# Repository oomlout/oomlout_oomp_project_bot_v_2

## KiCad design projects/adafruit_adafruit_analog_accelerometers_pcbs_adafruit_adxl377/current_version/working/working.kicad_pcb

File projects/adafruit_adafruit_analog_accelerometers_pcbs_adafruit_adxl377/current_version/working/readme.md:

# adafruit_analog_accelerometers_pcbs
 
## summary 
* id: adafruit_adafruit_analog_accelerometers_pcbs_adafruit_adxl377
* user: adafruit
* name: adafruit_analog_accelerometers_pcbs
* board: adafruit_adxl377
* repo: https://github.com/adafruit/Adafruit-Analog-Accelerometers-PCBs

* src_file_repo_sch: 
* src_file_repo_sch_link: https://github.com/adafruit/Adafruit-Analog-Accelerometers-PCBs/tree/master/
* full details link: https://github.com/oomlout/oomlout_oomp_project_bot_v_2/tree/main/projects/adafruit_adafruit_analog_accelerometers_pcbs_adafruit_adxl377/current_version/working  

## schematic  
  
[schematic (pdf)](working_schematic.pdf) 

## pcb  

[board (pdf)](working.pdf)  

## working_bom
| Id | Designator | Footprint | Quantity | Designation | Supplier and ref |  | None | 
| --- | --- | --- | --- | --- | --- | --- | --- | 
| 1 | C2,C3,C4 | C0805K | 3 | 0.1uF |  |  | [''] | 
| 2 | C5,C1 | C0805K | 2 | 10uF |  |  | [''] | 
| 3 | JP2 | 1X07_ROUND_76 | 1 |  |  |  | [''] | 
| 4 | U$5,U$8 | MOUNTINGHOLE_2.0_PLATED | 2 | MOUNTINGHOLE2.0 |  |  | [''] | 
| 5 | IC1 | 16LCSP | 1 | ADXL33X |  |  | [''] | 
| 6 | U$1,U$2 | FIDUCIAL_1MM | 2 | FIDUCIAL |  |  | [''] | 
| 7 | IC2 | SOT23-5L | 1 | LP298XS |  |  | [''] | 
| 8 | U$4 | ADAFRUIT_2.5MM | 1 |  |  |  | [''] | 

## bom_schematic
| Ref | Qnty | Value | Cmp name | Footprint | Description | Vendor | DNP | 
| --- | --- | --- | --- | --- | --- | --- | --- | 
| C1, C5 | 2 | 10uF | C-USC0805K | working:C0805K |  |  |  | 
| C2, C3, C4 | 3 | 0.1uF | C-USC0805K | working:C0805K |  |  |  | 
| IC1 | 1 | ADXL33X | ADXL33X | working:16LCSP |  |  |  | 
| IC2 | 1 | LP298XS | LP298XS | working:SOT23-5L |  |  |  | 
| JP2 | 1 | HEADER-1X7THICKER | HEADER-1X7THICKER | working:1X07_ROUND_76 |  |  |  | 
| U$1, U$2 | 2 | FIDUCIAL | FIDUCIAL | working:FIDUCIAL_1MM |  |  |  | 
| U$5, U$8 | 2 | MOUNTINGHOLE2.0 | MOUNTINGHOLE2.0 | working:MOUNTINGHOLE_2.0_PLATED |  |  |  | 

## mounting_holes
| x | y | package | value | ref | size | 
| --- | --- | --- | --- | --- | --- | 
| 13.97 | 0.0 | MOUNTINGHOLE_2.0_PLATED | MOUNTINGHOLE2.0 | U$5 | m3 | 
| 0.0 | 0.0 | MOUNTINGHOLE_2.0_PLATED | MOUNTINGHOLE2.0 | U$8 | m3 |

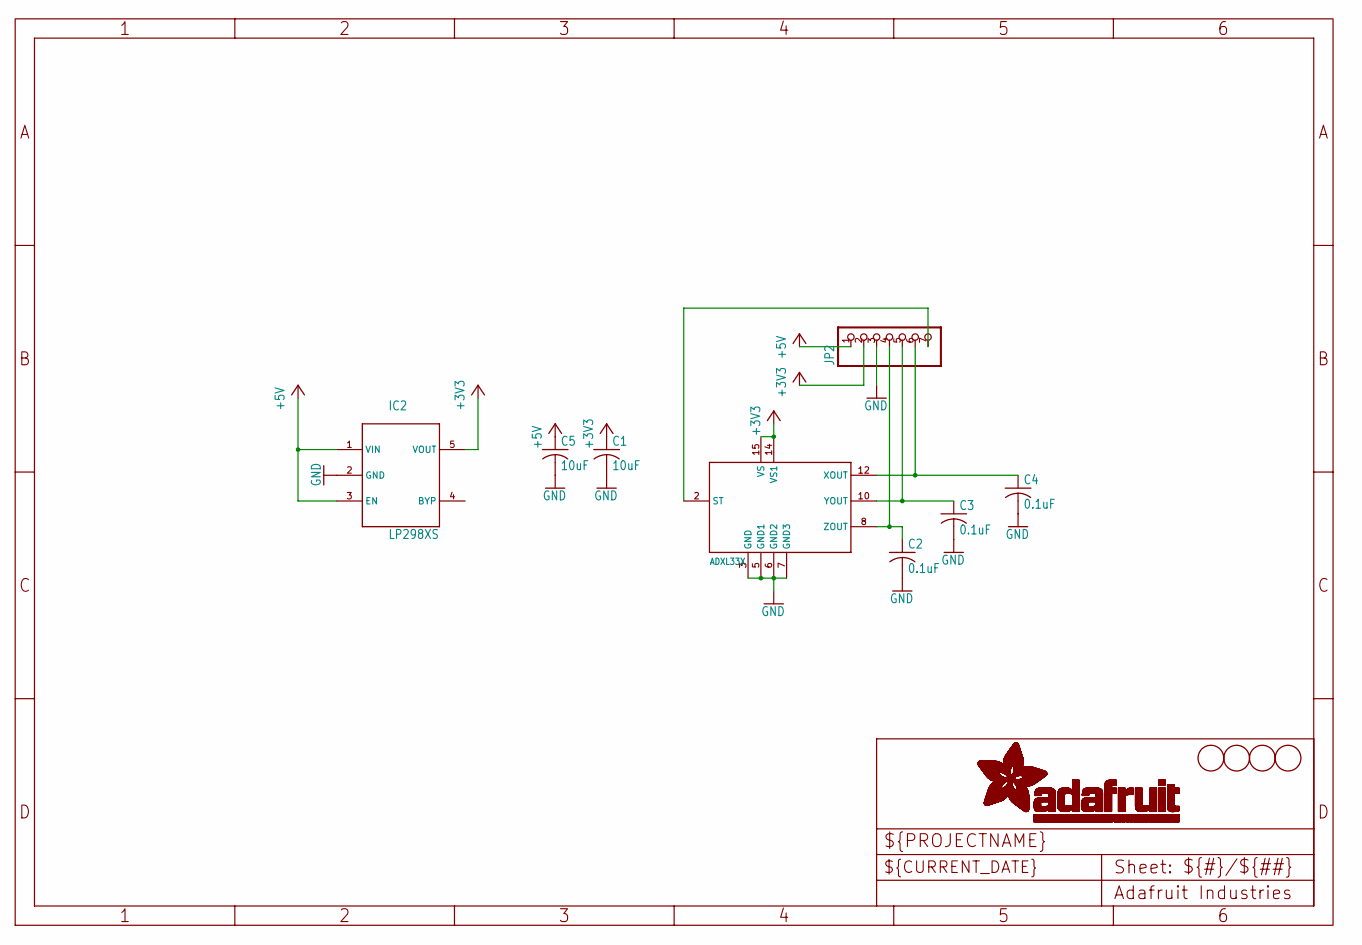
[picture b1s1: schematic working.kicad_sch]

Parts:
C1, C5: 10uF; C0805K
C2, C3, C4: 0.1uF; C0805K
IC1: ADXL33X; 16LCSP
IC2: LP298XS; SOT23-5L
JP2: HEADER-1X7THICKER; 1X07_ROUND_76
U$1, U$2: FIDUCIAL; FIDUCIAL_1MM
U$5, U$8: MOUNTINGHOLE2.0; MOUNTINGHOLE_2.0_PLATED

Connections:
+3V3: C1.1, IC1.14 (VS1), IC1.15 (VS), IC2.5 (VOUT), JP2.2
+5V: C5.1, IC2.1 (VIN), IC2.3 (EN), JP2.1
GND: C1.2, C2.2, C3.2, C4.2, C5.2, IC1.3 (GND), IC1.5 (GND1), IC1.6 (GND2), IC1.7 (GND3), IC2.2 (GND), JP2.3
ST: IC1.2 (ST), JP2.7
XOUT: C4.1, IC1.12 (XOUT), JP2.6
YOUT: C3.1, IC1.10 (YOUT), JP2.5
ZOUT: C2.1, IC1.8 (ZOUT), JP2.4

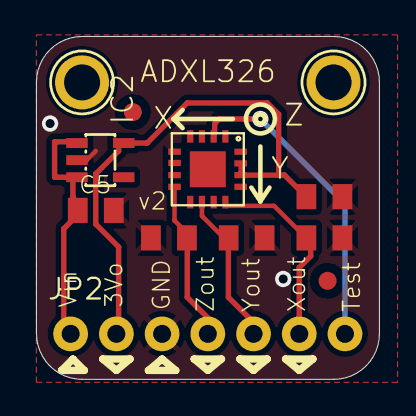
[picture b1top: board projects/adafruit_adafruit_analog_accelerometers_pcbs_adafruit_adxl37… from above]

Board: 16 copper layers, 19.1 x 19.1 mm, 13 parts (1 on the bottom side), 7 nets.

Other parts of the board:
U$4: ADAFRUIT_2.5MM

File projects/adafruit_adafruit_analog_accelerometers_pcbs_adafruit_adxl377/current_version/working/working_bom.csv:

"Id";"Designator";"Footprint";"Quantity";"Designation";"Supplier and ref";
1;"C2,C3,C4";"C0805K";3;"0.1uF";;;
2;"C5,C1";"C0805K";2;"10uF";;;
3;"JP2";"1X07_ROUND_76";1;"";;;
4;"U$5,U$8";"MOUNTINGHOLE_2.0_PLATED";2;"MOUNTINGHOLE2.0";;;
5;"IC1";"16LCSP";1;"ADXL33X";;;
6;"U$1,U$2";"FIDUCIAL_1MM";2;"FIDUCIAL";;;
7;"IC2";"SOT23-5L";1;"LP298XS";;;
8;"U$4";"ADAFRUIT_2.5MM";1;"";;;

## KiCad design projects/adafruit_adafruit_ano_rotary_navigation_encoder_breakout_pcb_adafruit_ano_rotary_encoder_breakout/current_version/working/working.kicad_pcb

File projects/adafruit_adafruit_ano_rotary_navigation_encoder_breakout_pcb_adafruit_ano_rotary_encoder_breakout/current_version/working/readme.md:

# adafruit_ano_rotary_navigation_encoder_breakout_pcb
 
## summary 
* id: adafruit_adafruit_ano_rotary_navigation_encoder_breakout_pcb_adafruit_ano_rotary_encoder_breakout
* user: adafruit
* name: adafruit_ano_rotary_navigation_encoder_breakout_pcb
* board: adafruit_ano_rotary_encoder_breakout
* repo: https://github.com/adafruit/Adafruit-ANO-Rotary-Navigation-Encoder-Breakout-PCB

* src_file_repo_sch: 
* src_file_repo_sch_link: https://github.com/adafruit/Adafruit-ANO-Rotary-Navigation-Encoder-Breakout-PCB/tree/main/
* full details link: https://github.com/oomlout/oomlout_oomp_project_bot_v_2/tree/main/projects/adafruit_adafruit_ano_rotary_navigation_encoder_breakout_pcb_adafruit_ano_rotary_encoder_breakout/current_version/working  

## schematic  
  
[schematic (pdf)](working_schematic.pdf) 

## pcb  

[board (pdf)](working.pdf)  

## working_bom
| Id | Designator | Footprint | Quantity | Designation | Supplier and ref |  | None | 
| --- | --- | --- | --- | --- | --- | --- | --- | 
| 1 | U$33 | PCBFEAT-REV-040 | 1 |  |  |  | [''] | 
| 2 | FID3,FID4 | FIDUCIAL_1MM | 2 | FIDUCIAL_1MM |  |  | [''] | 
| 3 | U$27,U$25,U$30,U$29 | MOUNTINGHOLE_2.5_PLATED | 4 | MOUNTINGHOLE2.5 |  |  | [''] | 
| 4 | JP3 | 1X09_ROUND_70 | 1 |  |  |  | [''] | 
| 5 | U$32 | ADAFRUIT_3.5MM | 1 |  |  |  | [''] | 
| 6 | X1 | ENCODER_ANO | 1 | ENCODER_ANO |  |  | [''] | 

## bom_schematic
| Ref | Qnty | Value | Cmp name | Footprint | Description | Vendor | DNP | 
| --- | --- | --- | --- | --- | --- | --- | --- | 
| FID3, FID4 | 2 | FIDUCIAL_1MM | FIDUCIAL_1MM | working:FIDUCIAL_1MM |  |  |  | 
| JP3 | 1 | HEADER-1X970MIL | HEADER-1X970MIL | working:1X09_ROUND_70 |  |  |  | 
| U$25, U$27, U$29, U$30 | 4 | MOUNTINGHOLE2.5 | MOUNTINGHOLE2.5 | working:MOUNTINGHOLE_2.5_PLATED |  |  |  | 
| X1 | 1 | ENCODER_ANO | ENCODER_ANO | working:ENCODER_ANO |  |  |  | 

## mounting_holes
| x | y | package | value | ref | size | 
| --- | --- | --- | --- | --- | --- | 
| 30.48 | 0.0 | MOUNTINGHOLE_2.5_PLATED | MOUNTINGHOLE2.5 | U$25 | m3 | 
| 0.0 | 0.0 | MOUNTINGHOLE_2.5_PLATED | MOUNTINGHOLE2.5 | U$27 | m3 | 
| 30.48 | 30.48 | MOUNTINGHOLE_2.5_PLATED | MOUNTINGHOLE2.5 | U$29 | m3 | 
| 0.0 | 30.48 | MOUNTINGHOLE_2.5_PLATED | MOUNTINGHOLE2.5 | U$30 | m3 |

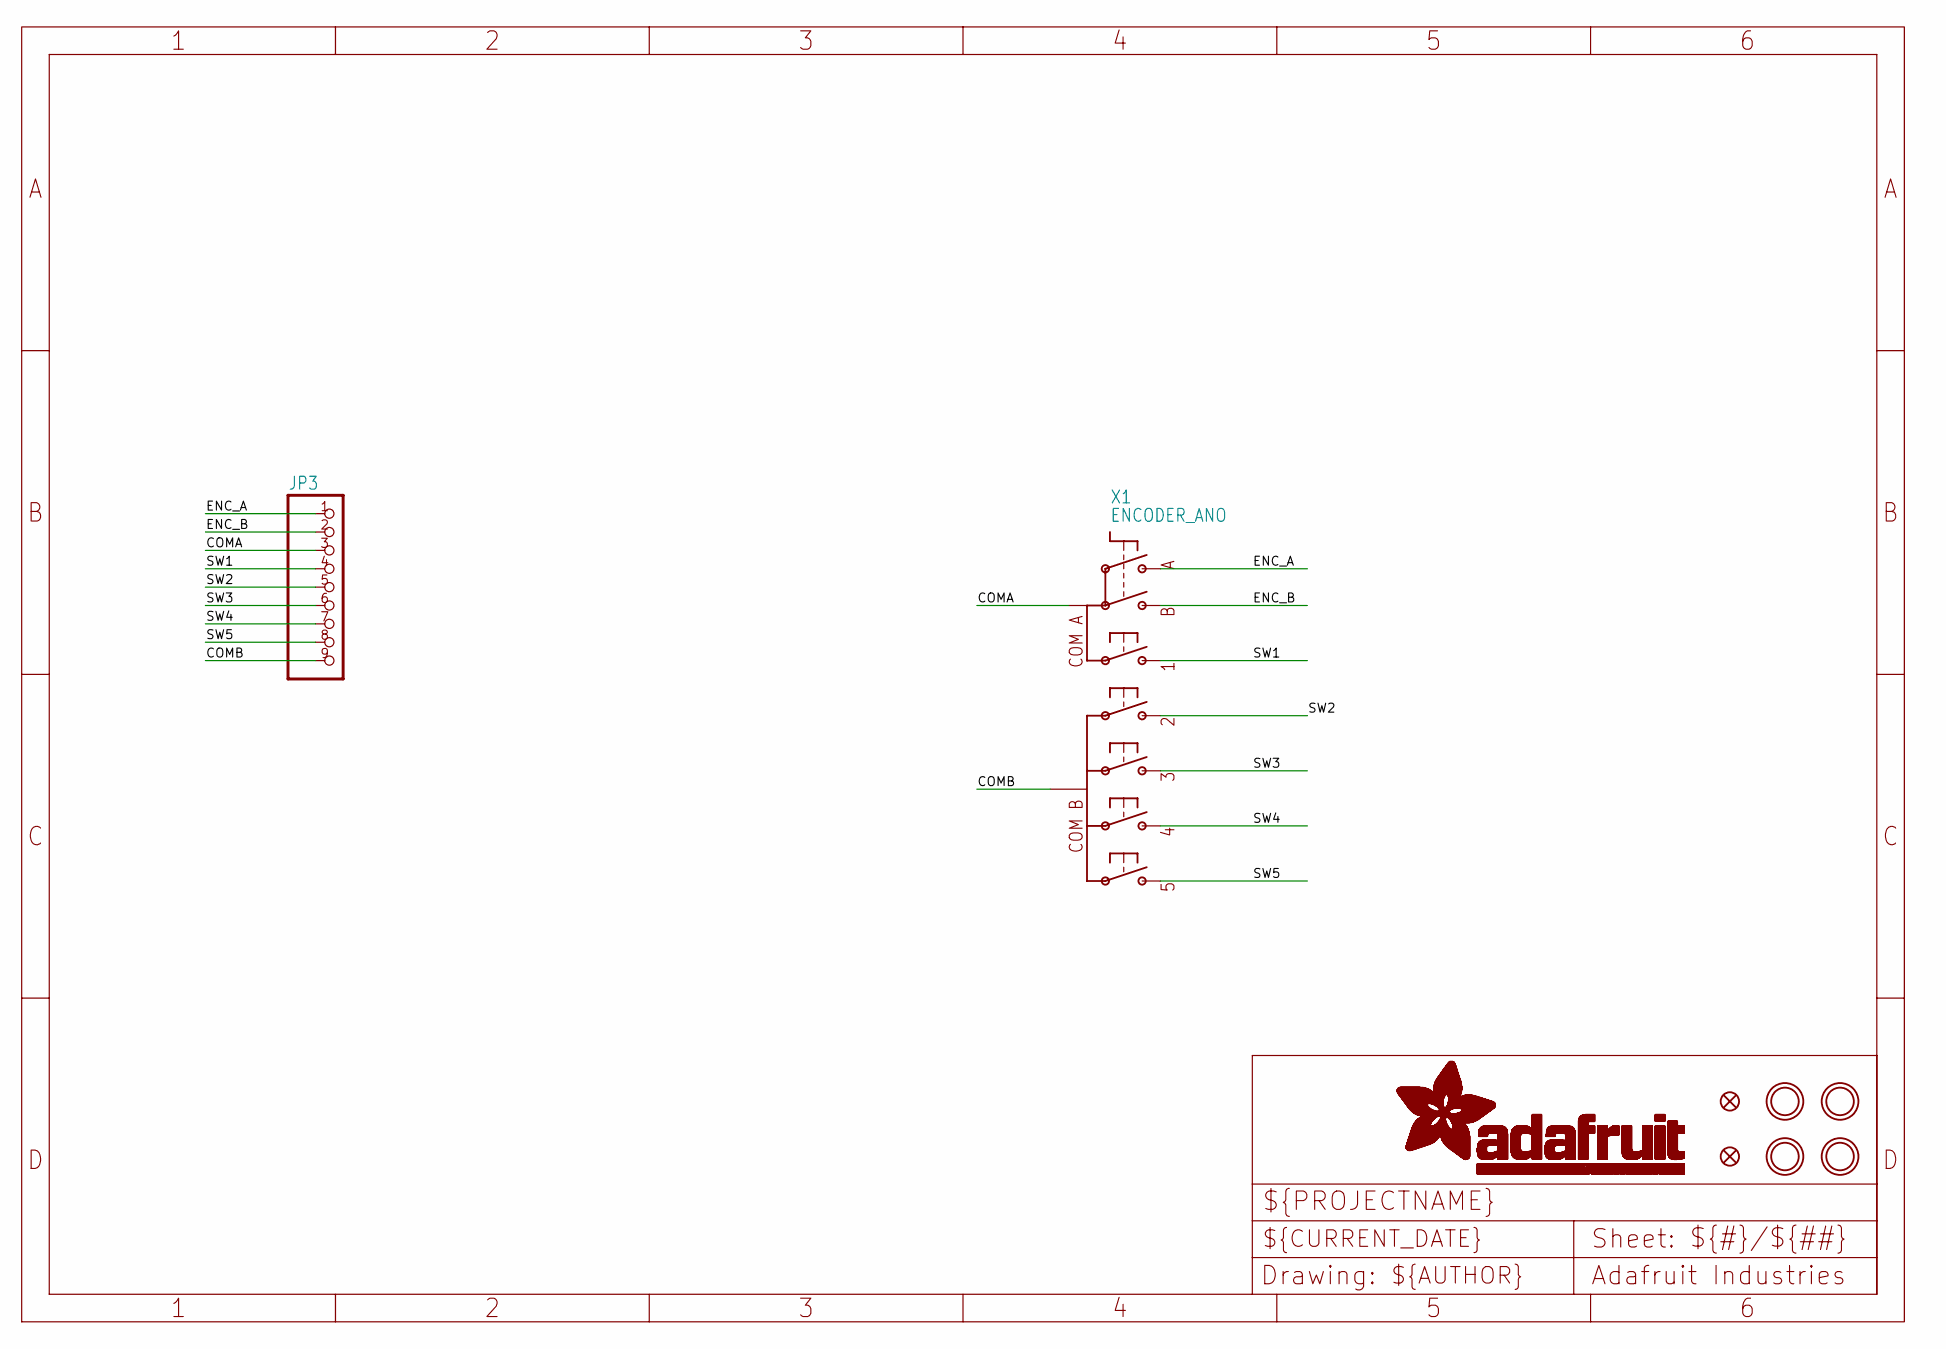
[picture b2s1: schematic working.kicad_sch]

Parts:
FID3, FID4: FIDUCIAL_1MM
JP3: HEADER-1X970MIL; 1X09_ROUND_70
U$25, U$27, U$29, U$30: MOUNTINGHOLE2.5; MOUNTINGHOLE_2.5_PLATED
X1: ENCODER_ANO

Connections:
COMA: JP3.3, X1.COM_A (COMA)
COMB: JP3.9, X1.COM_B
ENC_A: JP3.1, X1.A
ENC_B: JP3.2, X1.B
SW1: JP3.4, X1.S1 (1)
SW2: JP3.5, X1.S2
SW3: JP3.6, X1.S3
SW4: JP3.7, X1.S4
SW5: JP3.8, X1.S5

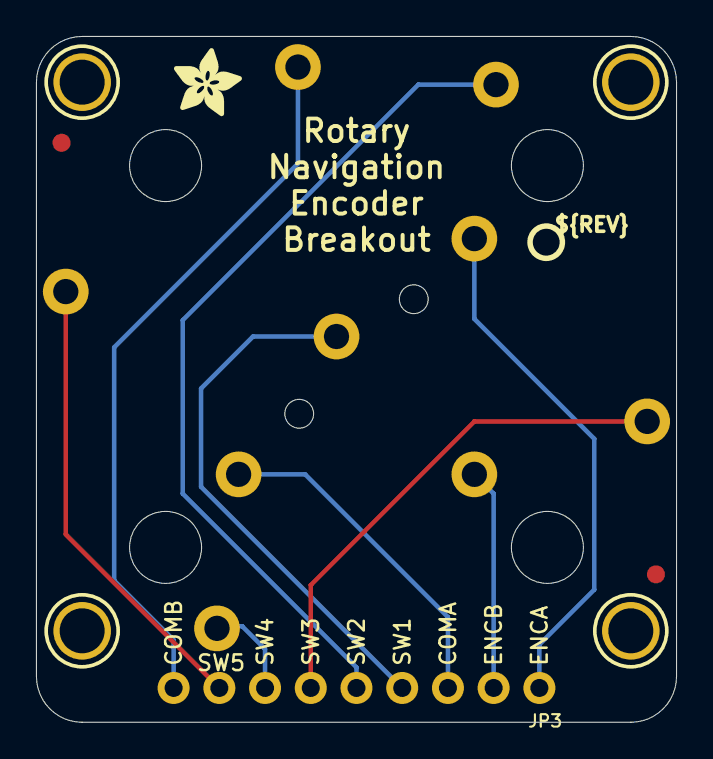
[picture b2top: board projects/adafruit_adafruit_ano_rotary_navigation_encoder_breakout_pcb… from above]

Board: 2 copper layers, 35.6 x 38.1 mm, 10 parts (1 on the bottom side), 9 nets.

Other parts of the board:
U$32: ADAFRUIT_3.5MM
U$33: PCBFEAT-REV-040

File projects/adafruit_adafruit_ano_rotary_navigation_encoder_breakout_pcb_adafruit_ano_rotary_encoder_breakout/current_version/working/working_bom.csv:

"Id";"Designator";"Footprint";"Quantity";"Designation";"Supplier and ref";
1;"U$33";"PCBFEAT-REV-040";1;"";;;
2;"FID3,FID4";"FIDUCIAL_1MM";2;"FIDUCIAL_1MM";;;
3;"U$27,U$25,U$30,U$29";"MOUNTINGHOLE_2.5_PLATED";4;"MOUNTINGHOLE2.5";;;
4;"JP3";"1X09_ROUND_70";1;"";;;
5;"U$32";"ADAFRUIT_3.5MM";1;"";;;
6;"X1";"ENCODER_ANO";1;"ENCODER_ANO";;;

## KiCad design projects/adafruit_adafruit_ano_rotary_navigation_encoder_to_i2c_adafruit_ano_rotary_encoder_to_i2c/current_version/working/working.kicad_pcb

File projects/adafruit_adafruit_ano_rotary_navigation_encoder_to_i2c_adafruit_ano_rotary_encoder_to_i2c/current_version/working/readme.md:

# adafruit_ano_rotary_navigation_encoder_to_i2c
 
## summary 
* id: adafruit_adafruit_ano_rotary_navigation_encoder_to_i2c_adafruit_ano_rotary_encoder_to_i2c
* user: adafruit
* name: adafruit_ano_rotary_navigation_encoder_to_i2c
* board: adafruit_ano_rotary_encoder_to_i2c
* repo: https://github.com/adafruit/Adafruit-ANO-Rotary-Navigation-Encoder-to-I2C

* src_file_repo_sch: 
* src_file_repo_sch_link: https://github.com/adafruit/Adafruit-ANO-Rotary-Navigation-Encoder-to-I2C/tree/main/
* full details link: https://github.com/oomlout/oomlout_oomp_project_bot_v_2/tree/main/projects/adafruit_adafruit_ano_rotary_navigation_encoder_to_i2c_adafruit_ano_rotary_encoder_to_i2c/current_version/working  

## schematic  
  
[schematic (pdf)](working_schematic.pdf) 

## pcb  

[board (pdf)](working.pdf)  

## working_bom
| Id | Designator | Footprint | Quantity | Designation | Supplier and ref |  | None | 
| --- | --- | --- | --- | --- | --- | --- | --- | 
| 1 | U$35,U$34 | STEMMAQT | 2 |  |  |  | [''] | 
| 2 | PLABEL10 | PLABEL10 | 1 |  |  |  | [''] | 
| 3 | FID3,FID4 | FIDUCIAL_1MM | 2 | FIDUCIAL_1MM |  |  | [''] | 
| 4 | U$30,U$29,U$25,U$27 | MOUNTINGHOLE_2.5_PLATED | 4 | MOUNTINGHOLE2.5 |  |  | [''] | 
| 5 | R4,R3,R1,R2,R7 | 0603-NO | 5 | 10K |  |  | [''] | 
| 6 | PLABEL4 | PLABEL4 | 1 |  |  |  | [''] | 
| 7 | PLABEL2 | PLABEL2 | 1 |  |  |  | [''] | 
| 8 | CONN4,CONN3 | JST_SH4 | 2 | STEMMA_I2C_QT |  |  | [''] | 
| 9 | U$2 | ADAFRUIT_5MM | 1 |  |  |  | [''] | 
| 10 | PLABEL9 | PLABEL9 | 1 |  |  |  | [''] | 
| 11 | X2 | QFN20_3MM | 1 | ATTINY8X6_QFN |  |  | [''] | 
| 12 | D1 | CHIPLED_0603_NOOUTLINE | 1 | GREEN |  |  | [''] | 
| 13 | SJ3,SJ2,SJ5,SJ4 | SOLDERJUMPER_CLOSEDWIRE | 4 |  |  |  | [''] | 
| 14 | C3,C2 | 0805-NO | 2 | 10uF |  |  | [''] | 
| 15 | D2 | CHIPLED_0603_NOOUTLINE | 1 | red |  |  | [''] | 
| 16 | PLABEL6 | PLABEL6 | 1 |  |  |  | [''] | 
| 17 | U$33 | PCBFEAT-REV-040 | 1 |  |  |  | [''] | 
| 18 | JP1 | 1X06_ROUND_70 | 1 |  |  |  | [''] | 
| 19 | PLABEL1 | PLABEL1 | 1 |  |  |  | [''] | 
| 20 | PLABEL0 | PLABEL0 | 1 |  |  |  | [''] | 
| 21 | R5 | RESPACK_4X0603 | 1 | 10K Pack |  |  | [''] | 
| 22 | PLABEL11 | PLABEL11 | 1 |  |  |  | [''] | 
| 23 | PLABEL3 | PLABEL3 | 1 |  |  |  | [''] | 
| 24 | PLABEL8 | PLABEL8 | 1 |  |  |  | [''] | 
| 25 | PLABEL5 | PLABEL5 | 1 |  |  |  | [''] | 
| 26 | PLABEL7 | PLABEL7 | 1 |  |  |  | [''] | 
| 27 | C4 | 0603-NO | 1 | 0.1uF |  |  | [''] | 
| 28 | E$2 | ADAFRUIT_2.5MM | 1 |  |  |  | [''] | 
| 29 | X1 | ENCODER_ANO | 1 | ENCODER_ANO |  |  | [''] | 

## bom_schematic
| Ref | Qnty | Value | Cmp name | Footprint | Description | Vendor | DNP | 
| --- | --- | --- | --- | --- | --- | --- | --- | 
| C2, C3 | 2 | 10uF | CAP_CERAMIC0805-NOOUTLINE | working:0805-NO |  |  |  | 
| C4 | 1 | 0.1uF | CAP_CERAMIC0603_NO | working:0603-NO |  |  |  | 
| CONN3, CONN4 | 2 | STEMMA_I2C_QT | STEMMA_I2C_QT | working:JST_SH4 |  |  |  | 
| D1 | 1 | GREEN | LED0603_NOOUTLINE | working:CHIPLED_0603_NOOUTLINE |  |  |  | 
| D2 | 1 | red | LED0603_NOOUTLINE | working:CHIPLED_0603_NOOUTLINE |  |  |  | 
| FID3, FID4 | 2 | FIDUCIAL_1MM | FIDUCIAL_1MM | working:FIDUCIAL_1MM |  |  |  | 
| JP1 | 1 | HEADER-1X670MIL | HEADER-1X670MIL | working:1X06_ROUND_70 |  |  |  | 
| R1, R2, R3, R4, R7 | 5 | 10K | RESISTOR_0603_NOOUT | working:0603-NO |  |  |  | 
| R5 | 1 | 10K Pack | RESISTOR_4PACK | working:RESPACK_4X0603 |  |  |  | 
| SJ2, SJ3, SJ4, SJ5 | 4 | SOLDERJUMPERCLOSED | SOLDERJUMPERCLOSED | working:SOLDERJUMPER_CLOSEDWIRE |  |  |  | 
| U$25, U$27, U$29, U$30 | 4 | MOUNTINGHOLE2.5 | MOUNTINGHOLE2.5 | working:MOUNTINGHOLE_2.5_PLATED |  |  |  | 
| X1 | 1 | ENCODER_ANO | ENCODER_ANO | working:ENCODER_ANO |  |  |  | 
| X2 | 1 | ATTINY8X6_QFN | ATTINY8X6_QFN | working:QFN20_3MM |  |  |  | 

## mounting_holes
| x | y | package | value | ref | size | 
| --- | --- | --- | --- | --- | --- | 
| 30.48 | 0.0 | MOUNTINGHOLE_2.5_PLATED | MOUNTINGHOLE2.5 | U$25 | m3 | 
| 0.0 | 0.0 | MOUNTINGHOLE_2.5_PLATED | MOUNTINGHOLE2.5 | U$27 | m3 | 
| 30.48 | 35.56 | MOUNTINGHOLE_2.5_PLATED | MOUNTINGHOLE2.5 | U$29 | m3 | 
| 0.0 | 35.56 | MOUNTINGHOLE_2.5_PLATED | MOUNTINGHOLE2.5 | U$30 | m3 |

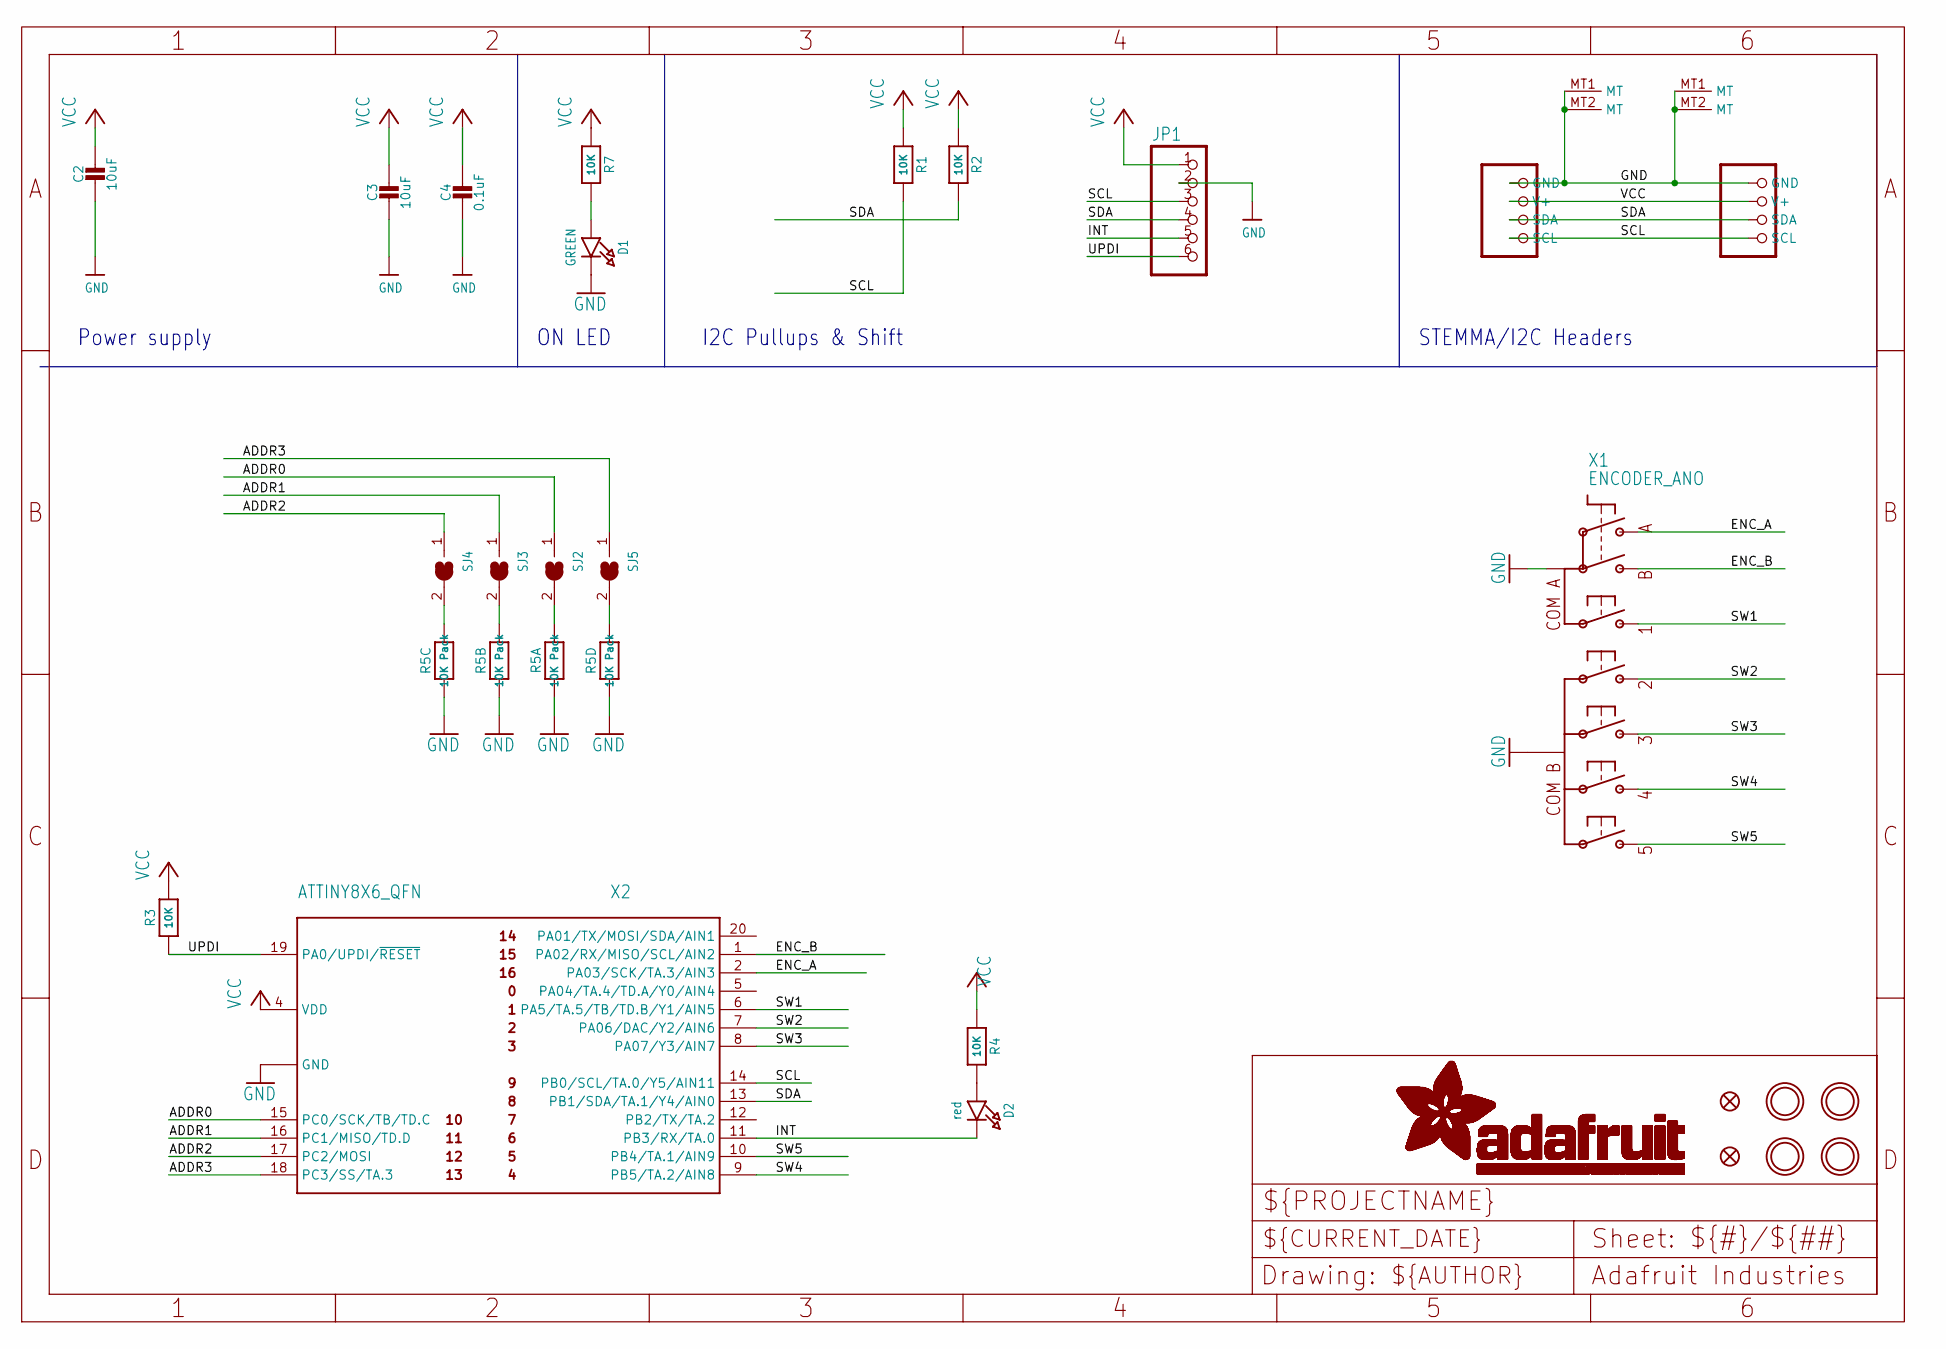
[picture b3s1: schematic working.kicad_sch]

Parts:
C2, C3: 10uF; 0805-NO
C4: 0.1uF; 0603-NO
CONN3, CONN4: STEMMA_I2C_QT; JST_SH4
D1: GREEN; CHIPLED_0603_NOOUTLINE
D2: red; CHIPLED_0603_NOOUTLINE
FID3, FID4: FIDUCIAL_1MM
JP1: HEADER-1X670MIL; 1X06_ROUND_70
R1, R2, R3, R4, R7: 10K; 0603-NO
R5: 10K Pack; RESPACK_4X0603
SJ2, SJ3, SJ4, SJ5: SOLDERJUMPERCLOSED; SOLDERJUMPER_CLOSEDWIRE
U$25, U$27, U$29, U$30: MOUNTINGHOLE2.5; MOUNTINGHOLE_2.5_PLATED
X1: ENCODER_ANO
X2: ATTINY8X6_QFN; QFN20_3MM

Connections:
ADDR0: SJ2.1, X2.15 (PC0/SCK/TB/TD.C)
ADDR1: SJ3.1, X2.16 (PC1/MISO/TD.D)
ADDR2: SJ4.1, X2.17 (PC2/MOSI)
ADDR3: SJ5.1, X2.18 (PC3/SS/TA.3)
ENC_A: X1.A, X2.2 (PA03/SCK/TA.3/AIN3)
ENC_B: X1.B, X2.1 (PA02/RX/MISO/SCL/AIN2)
GND: C2.2, C3.2, C4.2, CONN3.1 (GND), CONN3.MT1 (MT), CONN3.MT2 (MT), CONN4.1 (GND), CONN4.MT1 (MT), CONN4.MT2 (MT), D1.C, JP1.2, R5.1, R5.2 (1), R5.3 (1), R5.4 (1), X1.COM_A (COMA), X1.COM_B, X2.3 (GND), X2.PAD (GND)
INT: D2.C, JP1.5, X2.11 (PB3/RX/TA.0)
unnamed: D1.A, R7.2
unnamed: D2.A, R4.2
unnamed: R5.8 (2), SJ2.2
unnamed: R5.7 (2), SJ3.2
unnamed: R5.6 (2), SJ4.2
unnamed: R5.5 (2), SJ5.2
SCL: CONN3.4 (SCL), CONN4.4 (SCL), JP1.3, R1.2, X2.14 (PB0/SCL/TA.0/Y5/AIN11)
SDA: CONN3.3 (SDA), CONN4.3 (SDA), JP1.4, R2.2, X2.13 (PB1/SDA/TA.1/Y4/AIN0)
SW1: X1.S1 (1), X2.6 (PA5/TA.5/TB/TD.B/Y1/AIN5)
SW2: X1.S2, X2.7 (PA06/DAC/Y2/AIN6)
SW3: X1.S3, X2.8 (PA07/Y3/AIN7)
SW4: X1.S4, X2.9 (PB5/TA.2/AIN8)
SW5: X1.S5, X2.10 (PB4/TA.1/AIN9)
UPDI: JP1.6, R3.1, X2.19 (PA0/UPDI/~RESET)
VCC: C2.1, C3.1, C4.1, CONN3.2 (V+), CONN4.2 (V+), JP1.1, R1.1, R2.1, R3.2, R4.1, R7.1, X2.4 (VDD)

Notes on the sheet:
I2C Pullups & Shift
ON LED
STEMMA/I2C Headers
Power supply

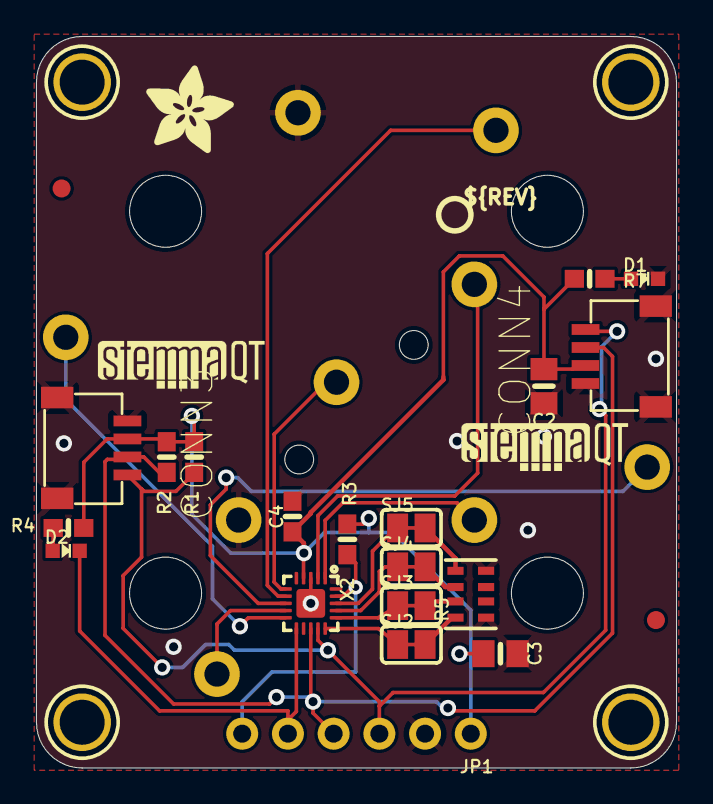
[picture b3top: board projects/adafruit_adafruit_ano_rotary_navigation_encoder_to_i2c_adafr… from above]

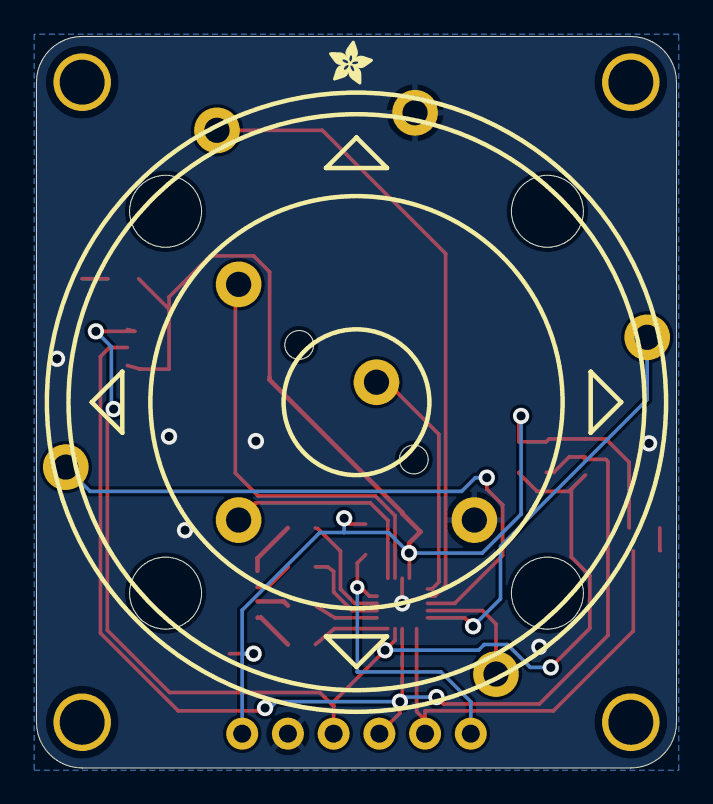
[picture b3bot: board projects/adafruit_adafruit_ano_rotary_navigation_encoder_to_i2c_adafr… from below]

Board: 2 copper layers, 35.6 x 40.6 mm, 43 parts (2 on the bottom side), 23 nets.

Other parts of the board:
E$2: ADAFRUIT_2.5MM
PLABEL0: PLABEL0
PLABEL1: PLABEL1
PLABEL2: PLABEL2
PLABEL3: PLABEL3
PLABEL4: PLABEL4
PLABEL5: PLABEL5
PLABEL6: PLABEL6
PLABEL7: PLABEL7
PLABEL8: PLABEL8
PLABEL9: PLABEL9
PLABEL10: PLABEL10
PLABEL11: PLABEL11
U$2: ADAFRUIT_5MM
U$33: PCBFEAT-REV-040
U$34, U$35: STEMMAQT

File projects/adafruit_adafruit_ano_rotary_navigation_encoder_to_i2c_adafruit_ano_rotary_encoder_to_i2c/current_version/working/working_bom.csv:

"Id";"Designator";"Footprint";"Quantity";"Designation";"Supplier and ref";
1;"U$35,U$34";"STEMMAQT";2;"";;;
2;"PLABEL10";"PLABEL10";1;"";;;
3;"FID3,FID4";"FIDUCIAL_1MM";2;"FIDUCIAL_1MM";;;
4;"U$30,U$29,U$25,U$27";"MOUNTINGHOLE_2.5_PLATED";4;"MOUNTINGHOLE2.5";;;
5;"R4,R3,R1,R2,R7";"0603-NO";5;"10K";;;
6;"PLABEL4";"PLABEL4";1;"";;;
7;"PLABEL2";"PLABEL2";1;"";;;
8;"CONN4,CONN3";"JST_SH4";2;"STEMMA_I2C_QT";;;
9;"U$2";"ADAFRUIT_5MM";1;"";;;
10;"PLABEL9";"PLABEL9";1;"";;;
11;"X2";"QFN20_3MM";1;"ATTINY8X6_QFN";;;
12;"D1";"CHIPLED_0603_NOOUTLINE";1;"GREEN";;;
13;"SJ3,SJ2,SJ5,SJ4";"SOLDERJUMPER_CLOSEDWIRE";4;"";;;
14;"C3,C2";"0805-NO";2;"10uF";;;
15;"D2";"CHIPLED_0603_NOOUTLINE";1;"red";;;
16;"PLABEL6";"PLABEL6";1;"";;;
17;"U$33";"PCBFEAT-REV-040";1;"";;;
18;"JP1";"1X06_ROUND_70";1;"";;;
19;"PLABEL1";"PLABEL1";1;"";;;
20;"PLABEL0";"PLABEL0";1;"";;;
21;"R5";"RESPACK_4X0603";1;"10K Pack";;;
22;"PLABEL11";"PLABEL11";1;"";;;
23;"PLABEL3";"PLABEL3";1;"";;;
24;"PLABEL8";"PLABEL8";1;"";;;
25;"PLABEL5";"PLABEL5";1;"";;;
26;"PLABEL7";"PLABEL7";1;"";;;
27;"C4";"0603-NO";1;"0.1uF";;;
28;"E$2";"ADAFRUIT_2.5MM";1;"";;;
29;"X1";"ENCODER_ANO";1;"ENCODER_ANO";;;

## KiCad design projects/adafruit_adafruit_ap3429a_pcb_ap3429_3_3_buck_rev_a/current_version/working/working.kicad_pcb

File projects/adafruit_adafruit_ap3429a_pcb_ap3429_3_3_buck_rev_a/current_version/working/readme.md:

# adafruit_ap3429a_pcb
 
## summary 
* id: adafruit_adafruit_ap3429a_pcb_ap3429_3_3_buck_rev_a
* user: adafruit
* name: adafruit_ap3429a_pcb
* board: ap3429_3_3_buck_rev_a
* repo: https://github.com/adafruit/Adafruit-AP3429A-PCB

* src_file_repo_sch: 
* src_file_repo_sch_link: https://github.com/adafruit/Adafruit-AP3429A-PCB/tree/main/
* full details link: https://github.com/oomlout/oomlout_oomp_project_bot_v_2/tree/main/projects/adafruit_adafruit_ap3429a_pcb_ap3429_3_3_buck_rev_a/current_version/working  

## schematic  
  
[schematic (pdf)](working_schematic.pdf) 

## pcb  

[board (pdf)](working.pdf)  

## bom_schematic
| Ref | Qnty | Value | Cmp name | Footprint | Description | Vendor | DNP | 
| --- | --- | --- | --- | --- | --- | --- | --- | 
| C1, C2, C3 | 3 | 22uF | CAP_CERAMIC0805-NOOUTLINE | working:0805-NO |  |  |  | 
| FID1 | 1 | FIDUCIAL_1MM | FIDUCIAL_1MM | working:FIDUCIAL_1MM |  |  |  | 
| IC1 | 1 | VREG_BUCK_5PIN_AP3429/A | VREG_BUCK_5PIN_AP3429/A | working:SOT23-5 |  |  |  | 
| JP1 | 1 | HEADER-1X4ROUND | HEADER-1X4ROUND | working:1X04_ROUND |  |  |  | 
| L1 | 1 | SDER041H-2R2MS | INDUCTORNRH2412T | working:INDUCTOR_TAIYOYUDEN_NRH2412T |  |  |  | 
| R1, R3 | 2 | 100K | RESISTOR_0603_NOOUT | working:0603-NO |  |  |  | 
| R2 | 1 | 450K | RESISTOR_0603_NOOUT | working:0603-NO |  |  |  | 
| U$9 | 1 | MOUNTINGHOLE2.5 | MOUNTINGHOLE2.5 | working:MOUNTINGHOLE_2.5_PLATED |  |  |  |

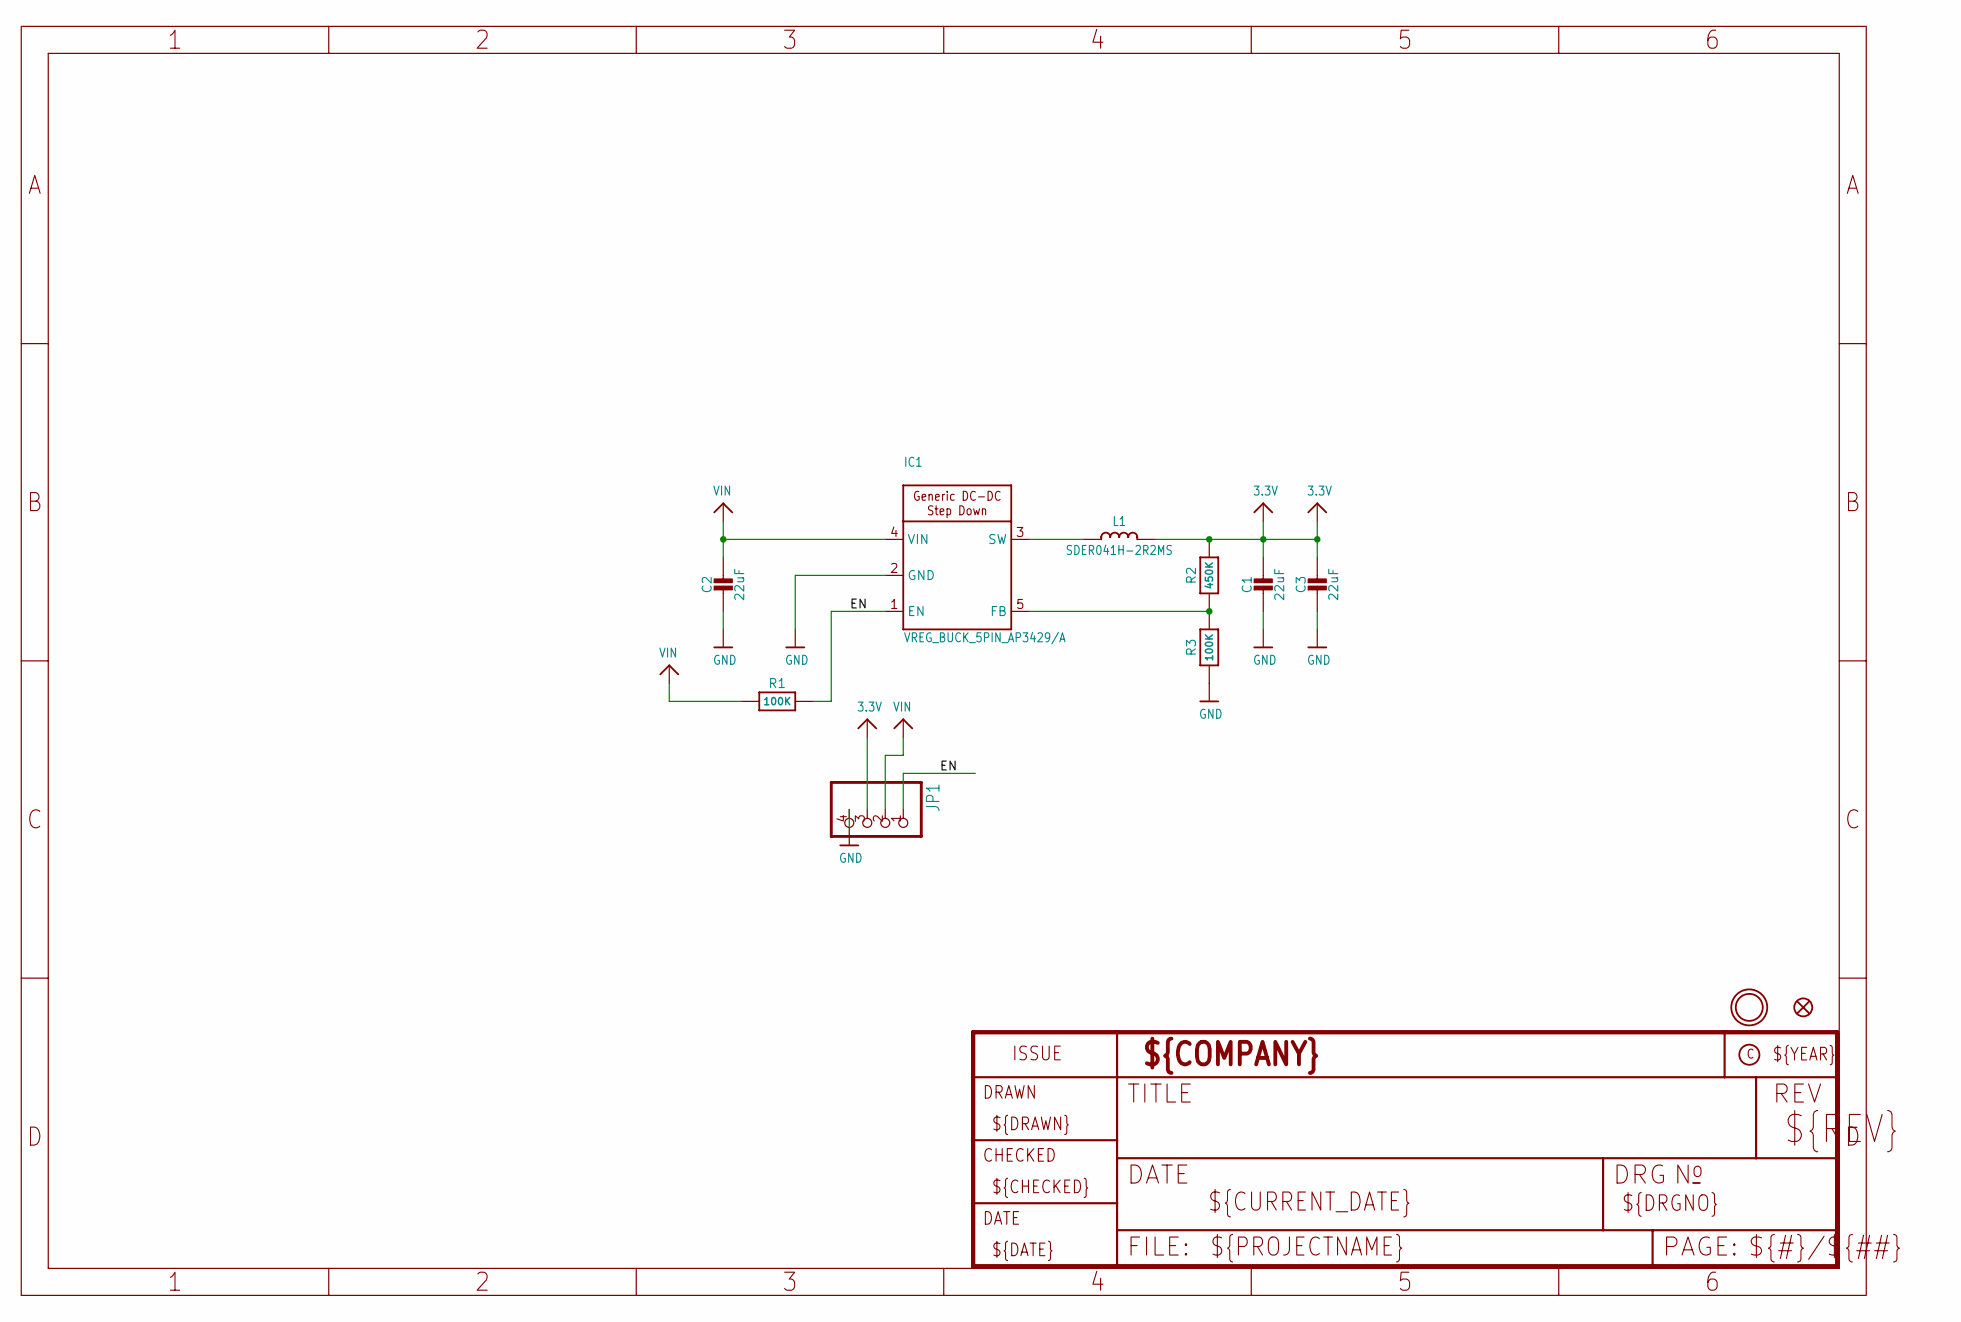
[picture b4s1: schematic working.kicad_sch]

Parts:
C1, C2, C3: 22uF; 0805-NO
FID1: FIDUCIAL_1MM
IC1: VREG_BUCK_5PIN_AP3429/A; SOT23-5
JP1: HEADER-1X4ROUND; 1X04_ROUND
L1: SDER041H-2R2MS; INDUCTOR_TAIYOYUDEN_NRH2412T
R1, R3: 100K; 0603-NO
R2: 450K; 0603-NO
U$9: MOUNTINGHOLE2.5; MOUNTINGHOLE_2.5_PLATED

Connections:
3.3V: C1.1, C3.1, JP1.3, L1.2, R2.2
EN: IC1.1 (EN), JP1.1, R1.2
FB: IC1.5 (FB), R2.1, R3.2
GND: C1.2, C2.2, C3.2, IC1.2 (GND), JP1.4, R3.1
unnamed: IC1.3 (SW), L1.1
VIN: C2.1, IC1.4 (VIN), JP1.2, R1.1

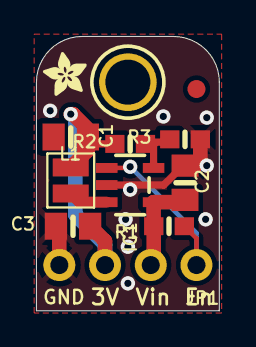
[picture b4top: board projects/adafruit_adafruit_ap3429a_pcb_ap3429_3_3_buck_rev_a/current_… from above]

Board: 2 copper layers, 10.2 x 15.2 mm, 13 parts (1 on the bottom side), 6 nets.

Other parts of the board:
U$10: PCBFEAT-REV-040
U$11: ADAFRUIT_2.5MM

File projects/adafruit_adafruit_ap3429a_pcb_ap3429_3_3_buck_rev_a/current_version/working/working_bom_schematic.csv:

"Source:","C:\gh\oomlout_oomp_project_bot_v_2\projects\adafruit_adafruit_ap3429a_pcb_ap3429_3_3_buck_rev_a\current_version\working\working.kicad_sch"
"Date:","09/09/2023 19:01:01"
"Tool:","Eeschema 7.0.6"
"Generator:","C:/Program Files/KiCad/7.0/bin/scripting/plugins/bom_csv_grouped_by_value_with_fp.py"
"Component Count:","11"
"Ref","Qnty","Value","Cmp name","Footprint","Description","Vendor","DNP"
"C1, C2, C3","3","22uF","CAP_CERAMIC0805-NOOUTLINE","working:0805-NO","","",""
"FID1","1","FIDUCIAL_1MM","FIDUCIAL_1MM","working:FIDUCIAL_1MM","","",""
"IC1","1","VREG_BUCK_5PIN_AP3429/A","VREG_BUCK_5PIN_AP3429/A","working:SOT23-5","","",""
"JP1","1","HEADER-1X4ROUND","HEADER-1X4ROUND","working:1X04_ROUND","","",""
"L1","1","SDER041H-2R2MS","INDUCTORNRH2412T","working:INDUCTOR_TAIYOYUDEN_NRH2412T","","",""
"R1, R3","2","100K","RESISTOR_0603_NOOUT","working:0603-NO","","",""
"R2","1","450K","RESISTOR_0603_NOOUT","working:0603-NO","","",""
"U$9","1","MOUNTINGHOLE2.5","MOUNTINGHOLE2.5","working:MOUNTINGHOLE_2.5_PLATED","","",""

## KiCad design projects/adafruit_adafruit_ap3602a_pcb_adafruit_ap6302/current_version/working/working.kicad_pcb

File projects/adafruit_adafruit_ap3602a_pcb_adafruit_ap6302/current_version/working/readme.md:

# adafruit_ap3602a_pcb
 
## summary 
* id: adafruit_adafruit_ap3602a_pcb_adafruit_ap6302
* user: adafruit
* name: adafruit_ap3602a_pcb
* board: adafruit_ap6302
* repo: https://github.com/adafruit/Adafruit-AP3602A-PCB

* src_file_repo_sch: 
* src_file_repo_sch_link: https://github.com/adafruit/Adafruit-AP3602A-PCB/tree/master/
* full details link: https://github.com/oomlout/oomlout_oomp_project_bot_v_2/tree/main/projects/adafruit_adafruit_ap3602a_pcb_adafruit_ap6302/current_version/working  

## schematic  
  
[schematic (pdf)](working_schematic.pdf) 

## pcb  

[board (pdf)](working.pdf)  

## working_bom
| Id | Designator | Footprint | Quantity | Designation | Supplier and ref |  | None | 
| --- | --- | --- | --- | --- | --- | --- | --- | 
| 1 | C3 | 0805-NO | 1 | 1uF |  |  | [''] | 
| 2 | C2,C1 | 0805-NO | 2 | 10uF |  |  | [''] | 
| 3 | JP1 | 1X04_ROUND | 1 |  |  |  | [''] | 
| 4 | U$9 | MOUNTINGHOLE_2.5_PLATED | 1 | MOUNTINGHOLE2.5 |  |  | [''] | 
| 5 | FID1 | FIDUCIAL_1MM | 1 | FIDUCIAL" |  |  | [''] | 
| 6 | U$11 | ADAFRUIT_2.5MM | 1 |  |  |  | [''] | 
| 7 | IC1 | SOT23-6 | 1 | AP3602 |  |  | [''] | 
| 8 | R1 | 0805-NO | 1 | 100K |  |  | [''] | 
| 9 | U$10 | PCBFEAT-REV-040 | 1 |  |  |  | [''] | 

## bom_schematic
| Ref | Qnty | Value | Cmp name | Footprint | Description | Vendor | DNP | 
| --- | --- | --- | --- | --- | --- | --- | --- | 
| C1, C2 | 2 | 10uF | CAP_CERAMIC0805-NOOUTLINE | working:0805-NO |  |  |  | 
| C3 | 1 | 1uF | CAP_CERAMIC0805-NOOUTLINE | working:0805-NO |  |  |  | 
| FID1 | 1 | FIDUCIAL"" | FIDUCIAL{dblquote}{dblquote} | working:FIDUCIAL_1MM |  |  |  | 
| IC1 | 1 | AP3602 | AP3602 | working:SOT23-6 |  |  |  | 
| JP1 | 1 | HEADER-1X4ROUND | HEADER-1X4ROUND | working:1X04_ROUND |  |  |  | 
| R1 | 1 | 100K | RESISTOR0805_NOOUTLINE | working:0805-NO |  |  |  | 
| U$9 | 1 | MOUNTINGHOLE2.5 | MOUNTINGHOLE2.5 | working:MOUNTINGHOLE_2.5_PLATED |  |  |  | 

## mounting_holes
| x | y | package | value | ref | size | 
| --- | --- | --- | --- | --- | --- | 
| 0.0 | 0.0 | MOUNTINGHOLE_2.5_PLATED | MOUNTINGHOLE2.5 | U$9 | m3 |

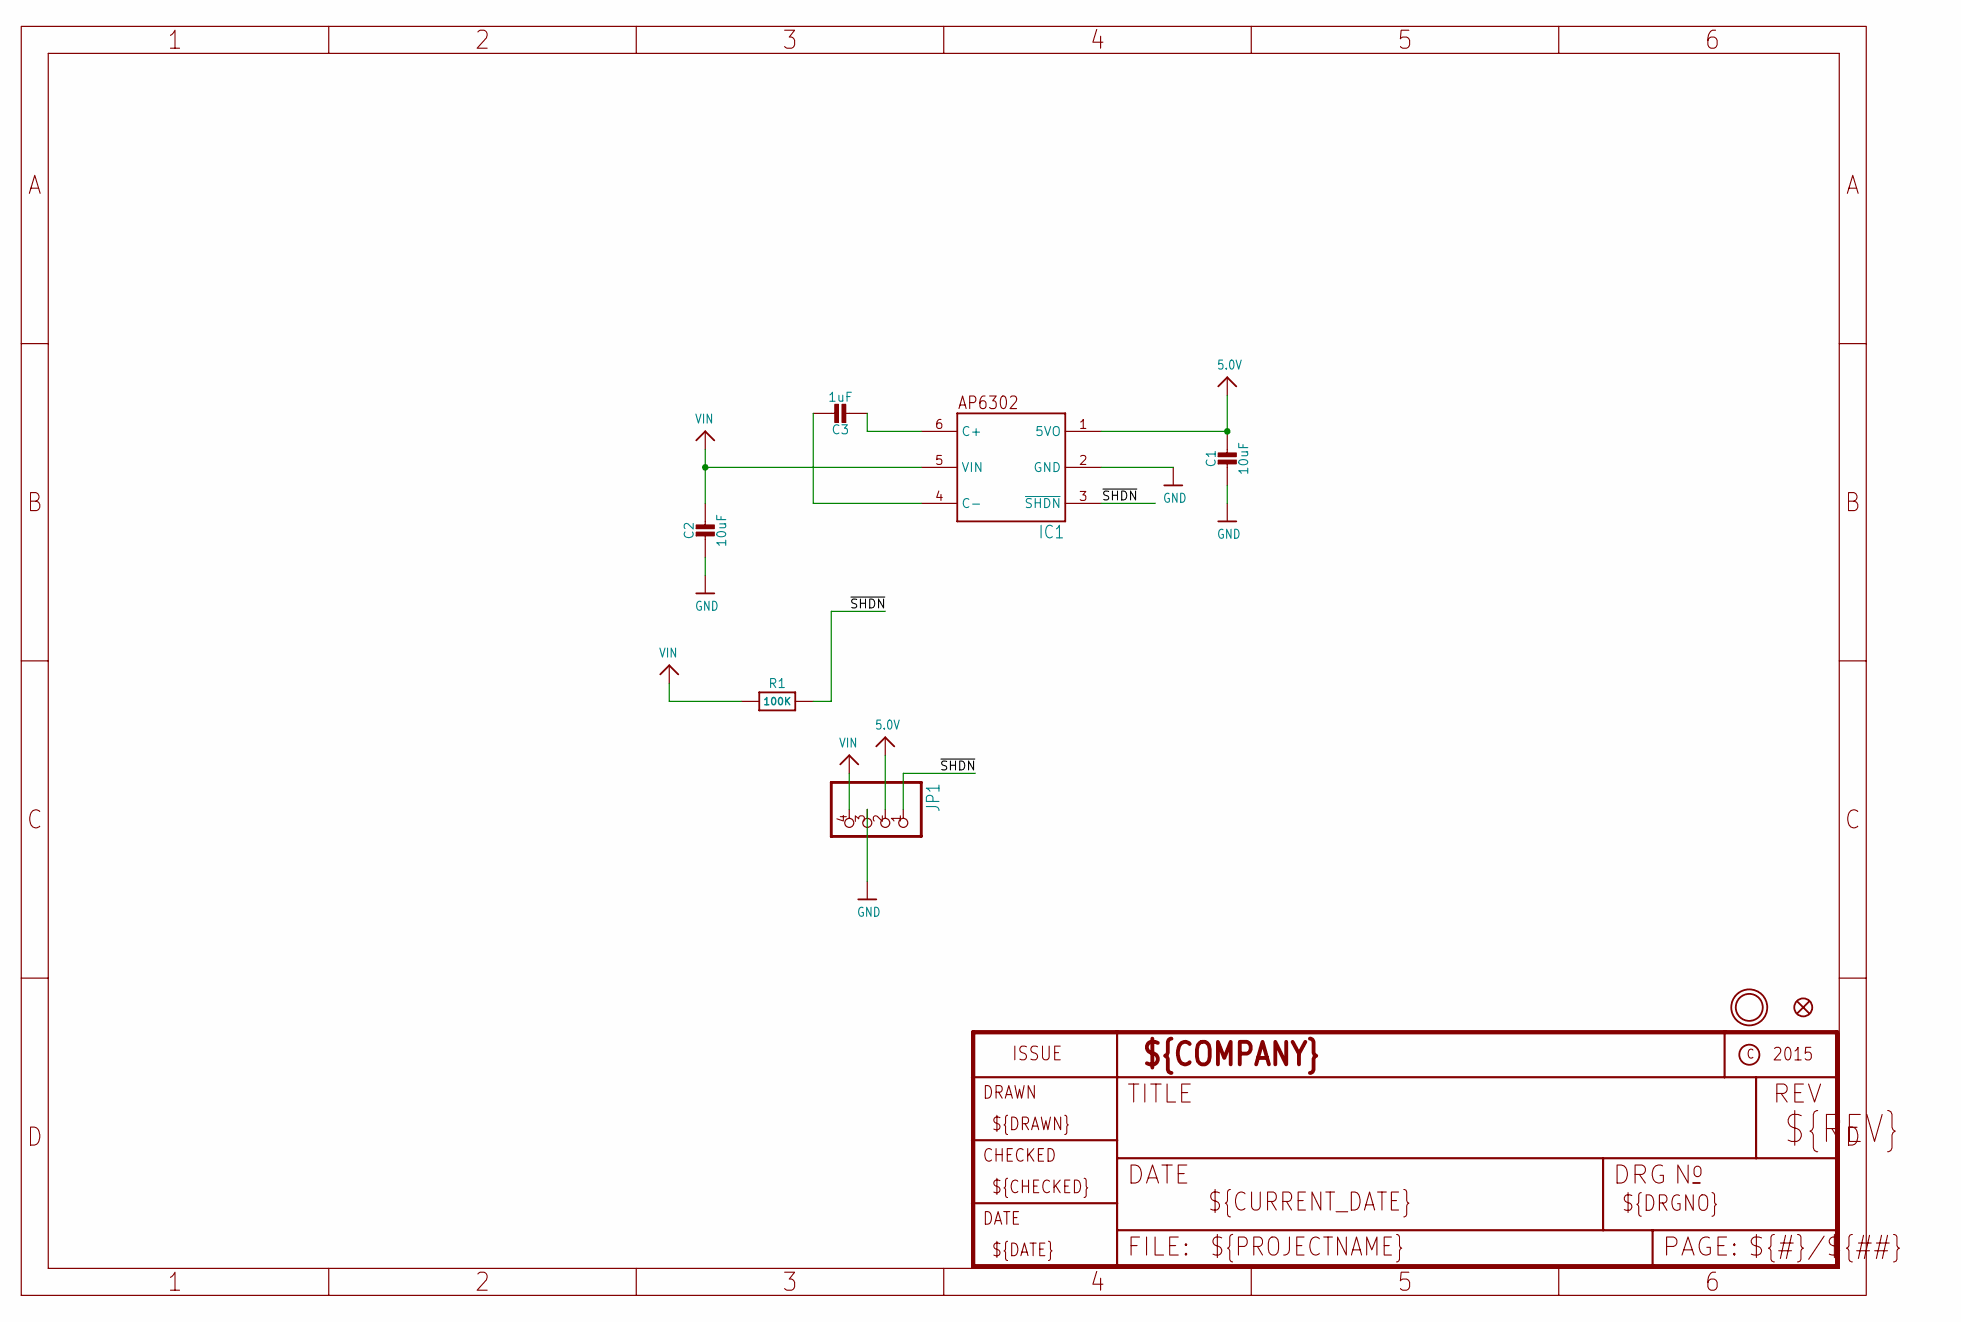
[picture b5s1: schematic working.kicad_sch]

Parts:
C1, C2: 10uF; 0805-NO
C3: 1uF; 0805-NO
FID1: FIDUCIAL""; FIDUCIAL_1MM
IC1: AP3602; SOT23-6
JP1: HEADER-1X4ROUND; 1X04_ROUND
R1: 100K; 0805-NO
U$9: MOUNTINGHOLE2.5; MOUNTINGHOLE_2.5_PLATED

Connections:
5.0V: C1.1, IC1.1 (5VO), JP1.2
GND: C1.2, C2.2, IC1.2 (GND), JP1.3
unnamed: C3.2, IC1.6 (C+)
unnamed: C3.1, IC1.4 (C-)
VIN: C2.1, IC1.5 (VIN), JP1.4, R1.1
~SHDN: IC1.3 (~SHDN), JP1.1, R1.2

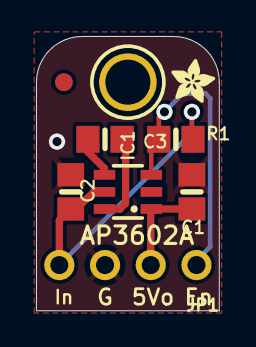
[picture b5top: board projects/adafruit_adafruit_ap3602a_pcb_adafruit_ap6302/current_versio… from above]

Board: 2 copper layers, 10.2 x 15.2 mm, 10 parts (1 on the bottom side), 6 nets.

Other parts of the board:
U$10: PCBFEAT-REV-040
U$11: ADAFRUIT_2.5MM

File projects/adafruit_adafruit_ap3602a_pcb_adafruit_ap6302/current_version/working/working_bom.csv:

"Id";"Designator";"Footprint";"Quantity";"Designation";"Supplier and ref";
1;"C3";"0805-NO";1;"1uF";;;
2;"C2,C1";"0805-NO";2;"10uF";;;
3;"JP1";"1X04_ROUND";1;"";;;
4;"U$9";"MOUNTINGHOLE_2.5_PLATED";1;"MOUNTINGHOLE2.5";;;
5;"FID1";"FIDUCIAL_1MM";1;"FIDUCIAL""";;;
6;"U$11";"ADAFRUIT_2.5MM";1;"";;;
7;"IC1";"SOT23-6";1;"AP3602";;;
8;"R1";"0805-NO";1;"100K";;;
9;"U$10";"PCBFEAT-REV-040";1;"";;;
